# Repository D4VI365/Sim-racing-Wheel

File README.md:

# Sim racing Wheel
I'm building a custom direct drive force feedback wheel for simracing

The device is powered by a 24V Power supply. It is a direct drive force feedback sim racing wheels that can theoretically deliver up to 15Nm of torque. It uses a 6.5" hoverboard motor, an ODESK V4.2 and a 500Pr E6B2-CWZ6C encoder with a 3:1 ratio to have a better resolution. for the software I'm using the FFBeats software and a custom written program to control the buttons. They have a separate custom board to have a simpler and more manageable interface. All the pieces are assembled using M6 nuts and bolts except from the grips and the belt tensioner that use M3 screws and heat inserts.

Full assembly:

Wheel:

PCB layout:

Electrical scheme:

| Name                       | Purpose                                    | Quantity | Total Cost (USD) | Link                                                                                                                                                                                                                                                                                                                                                                                | Distributor |
|----------------------------|--------------------------------------------|----------|------------------|-------------------------------------------------------------------------------------------------------------------------------------------------------------------------------------------------------------------------------------------------------------------------------------------------------------------------------------------------------------------------------------|-------------|
| M6 threaded rod            | making the inclination adjustable          | 1        | 4.60             | https://it.aliexpress.com/item/1005008168724880.html?spm=a2g0o.productlist.main.1.407b1a78dan9Kn&algo_pvid=5741f0d9-b67d-4d66-b3fc-48066c28b168&pdp_ext_f=%7B%22order%22%3A%229197%22%2C%22spu_best_type%22%3A%22price%22%2C%22eval%22%3A%221%22%2C%22fromPage%22%3A%22search%22%7D&utparam-url=scene%3Asearch%7Cquery_from%3A%7Cx_object_id%3A1005008168724880%7C_p_origin_prod%3A | Aliexpress  |
| M6 nuts and bolts          | holding the pieces together                | 1        | 8.19             | https://it.aliexpress.com/item/1005011593584495.html?pdp_ext_f=%7B%22sku_id%22%3A%2212000056008441829%22%7D&sourceType=1&spm=a2g0o.wish-manage-home.0.0&gatewayAdapt=glo2ita                                                                                                                                                                                                        | Aliexpress  |
| PCB                        | Connecting and controlling all the buttons | 1        | 2.00             | https://jlcpcb.com                                                                                                                                                                                                                                                                                                                                                                  | JLCPCB      |
| 6.5"" 350W brushless motor | Force feedback motor                       | 1        | 45.00            | https://www.aliexpress.com/item/1005010742922270.html?spm=a2g0o.cart.0.0.252f18fc3qqzs7&mp=1                                                                                                                                                                                                                                                                                        | Vinted      |
| 500PR E6B2-CWZ6C           | obtaining the wheel position               | 1        | 25.20            | https://www.aliexpress.com/item/1005009080411213.html?spm=a2g0o.cart.0.0.252f18fc3qqzs7&mp=1                                                                                                                                                                                                                                                                                        | Aliexpress  |
| Odesk v4.2                 | Motor driver                               | 1        | 46.65            | https://www.aliexpress.com/item/1005005725467528.html?spm=a2g0o.cart.0.0.252f18fc3qqzs7&mp=1                                                                                                                                                                                                                                                                                        | Aliexpress  |
| 16mm Button                | Utility buttons                            | 8        | 4.86             | https://www.aliexpress.com/item/1005008839427718.html?spm=a2g0o.cart.0.0.252f18fc3qqzs7&mp=1                                                                                                                                                                                                                                                                                        | Aliexpress  |
| 2GT 20T pulley             | transmitting power to the encoder          | 1        | 3.25             | https://www.aliexpress.com/item/1005006217674592.html?spm=a2g0o.cart.0.0.252f18fc3qqzs7&mp=1                                                                                                                                                                                                                                                                                        | Aliexpress  |
| Teethless 2GT 20T pulley   | tensioning the belt                        | 1        | 2.67             | https://www.aliexpress.com/item/1005006739452921.html?spm=a2g0o.cart.0.0.252f18fc3qqzs7&mp=1                                                                                                                                                                                                                                                                                        | Aliexpress  |
| limit switch               | paddles buttons                            | 4        | 4.51             | https://www.aliexpress.com/item/32273125391.html?spm=a2g0o.cart.0.0.252f18fc3qqzs7&mp=1                                                                                                                                                                                                                                                                                             | Aliexpress  |
| 10x10x2 magnets            | magnetic paddles                           | 4        | 3.13             | https://www.aliexpress.com/item/1005010075198458.html?spm=a2g0o.cart.0.0.252f18fc3qqzs7&mp=1                                                                                                                                                                                                                                                                                        | Aliexpress  |
| 10-280mm 2GT belt          | transmitting power to the encoder          | 1        | 1.86             | https://www.aliexpress.com/item/1005009550451001.html?spm=a2g0o.cart.0.0.252f18fc3qqzs7&mp=1                                                                                                                                                                                                                                                                                        | Aliexpress  |
| 12V 400W PSU               | Powering the wheel                         | 1        | 28.08            | https://www.aliexpress.com/item/1005008642209328.html?spm=a2g0o.cart.0.0.252f18fc3qqzs7&mp=1                                                                                                                                                                                                                                                                                        | Aliexpress  |
| Arduino pro nano           | Controlling the buttons interface board    | 1        | 4.18             | https://www.aliexpress.com/item/1005006438510487.html?spm=a2g0o.cart.0.0.252f18fc3qqzs7&mp=1                                                                                                                                                                                                                                                                                        | Aliexpress  |
| XT60 Connectors            | Bringing power from the PSU                | 1        | 1.58             | https://www.aliexpress.com/item/1005007356557188.html?spm=a2g0o.cart.0.0.252f18fc3qqzs7&mp=1                                                                                                                                                                                                                                                                                        | Aliexpress  |

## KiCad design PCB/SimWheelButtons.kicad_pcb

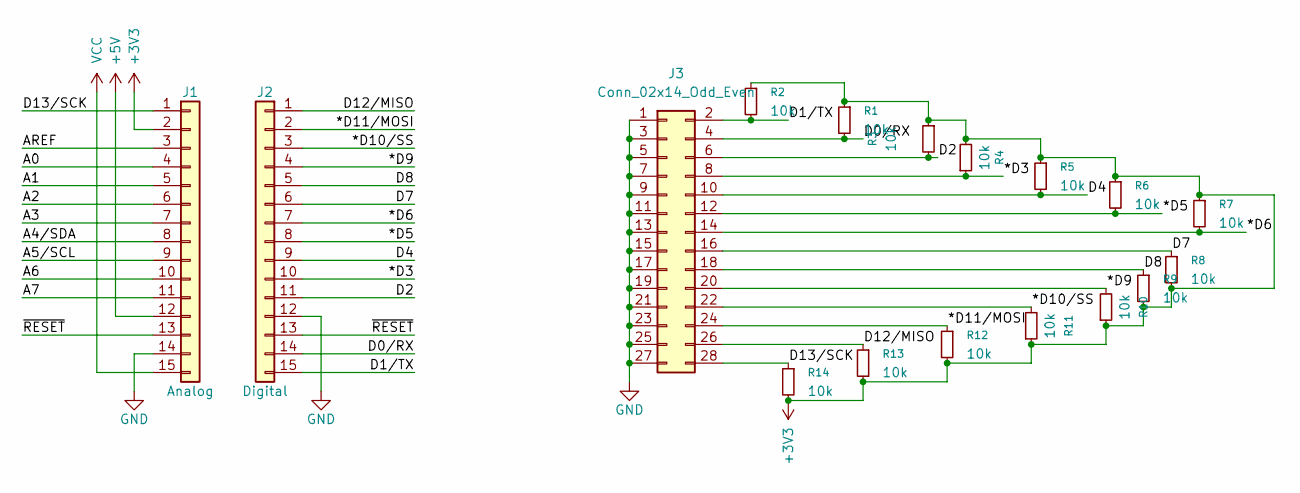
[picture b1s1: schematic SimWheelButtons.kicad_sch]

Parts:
J1: Analog; PinHeader_1x15_P2.54mm_Vertical
J2: Digital; PinHeader_1x15_P2.54mm_Vertical
J3: Conn_02x14_Odd_Even; PinHeader_2x14_P2.54mm_Vertical
R1, R2, R3, R4, R5, R6, R7, R8, R9, R10, R11, R12, R13, R14: 10k; R_0805_2012Metric_Pad1.20x1.40mm_HandSolder

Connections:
+3V3: J1.2, R1.1, R2.1, R3.1, R4.2, R5.1, R6.1, R7.1, R8.2, R9.2, R10.1, R11.1, R12.2, R13.2, R14.2
+5V: J1.12
/*D3: J2.10, J3.8, R4.1
/*D5: J2.8, J3.12, R6.2
/*D6: J2.7, J3.14, R7.2
/*D9: J2.4, J3.20, R10.2
/*D10/SS: J2.3, J3.22, R11.2
/*D11/MOSI: J2.2, J3.24, R12.1
/A0: J1.4
/A1: J1.5
/A2: J1.6
/A3: J1.7
/A4/SDA: J1.8
/A5/SCL: J1.9
/A6: J1.10
/A7: J1.11
/AREF: J1.3
/D0/RX: J2.14, J3.4, R1.2
/D1/TX: J2.15, J3.2, R2.2
/D2: J2.11, J3.6, R3.2
/D4: J2.9, J3.10, R5.2
/D7: J2.6, J3.16, R8.1
/D8: J2.5, J3.18, R9.1
/D12/MISO: J2.1, J3.26, R13.1
/D13/SCK: J1.1, J3.28, R14.1
/~RESET: J1.13, J2.13
GND: J1.14, J2.12, J3.1, J3.3, J3.5, J3.7, J3.9, J3.11, J3.13, J3.15, J3.17, J3.19, J3.21, J3.23, J3.25, J3.27
VCC: J1.15

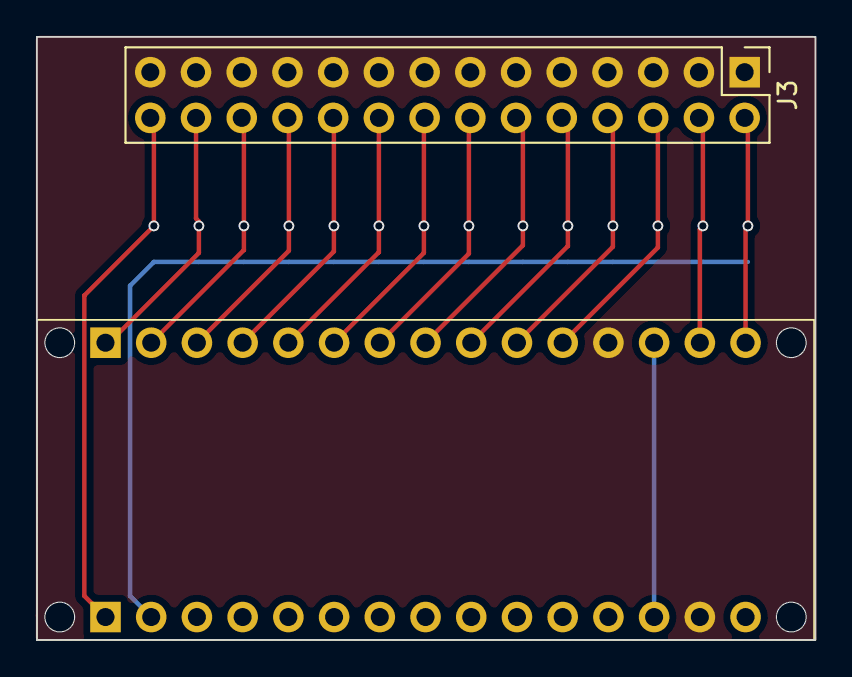
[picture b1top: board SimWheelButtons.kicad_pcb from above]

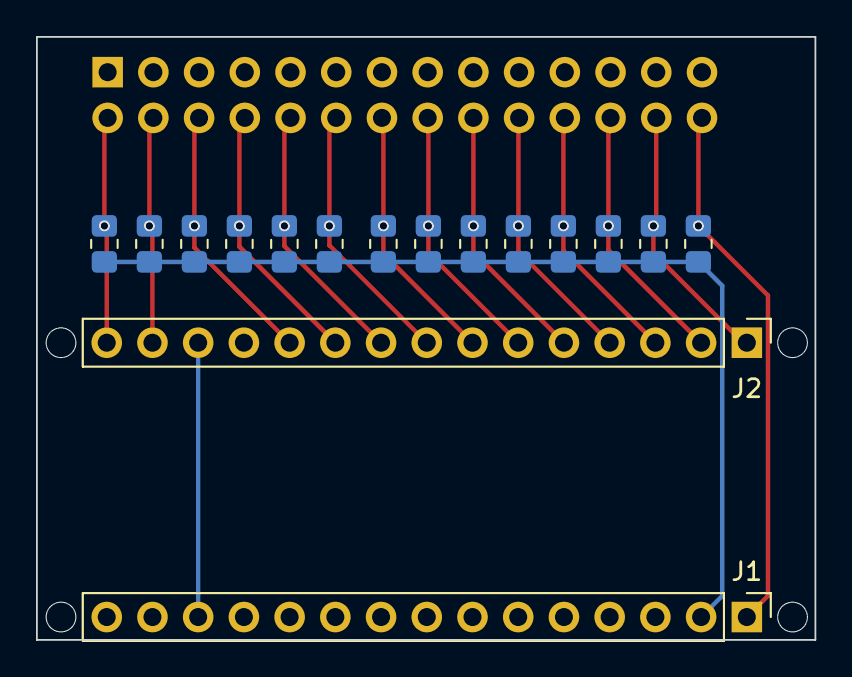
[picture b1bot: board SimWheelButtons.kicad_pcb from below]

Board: 2 copper layers, 43.2 x 33.5 mm, 21 parts (16 on the bottom side), 17 nets.

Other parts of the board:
MH1, MH2, MH3, MH4: MountingHole_65mil

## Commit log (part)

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2026-05-13 push
2026-06-04 Add Gerber production files for PCB
    Add complete Gerber output for the SimWheelButtons PCB to PCB/Production. Includes top/bottom copper, soldermask, paste, silkscreen, edge cuts, NPTH/PTH drill files, .gbrjob and a Gerber.zip archive.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
